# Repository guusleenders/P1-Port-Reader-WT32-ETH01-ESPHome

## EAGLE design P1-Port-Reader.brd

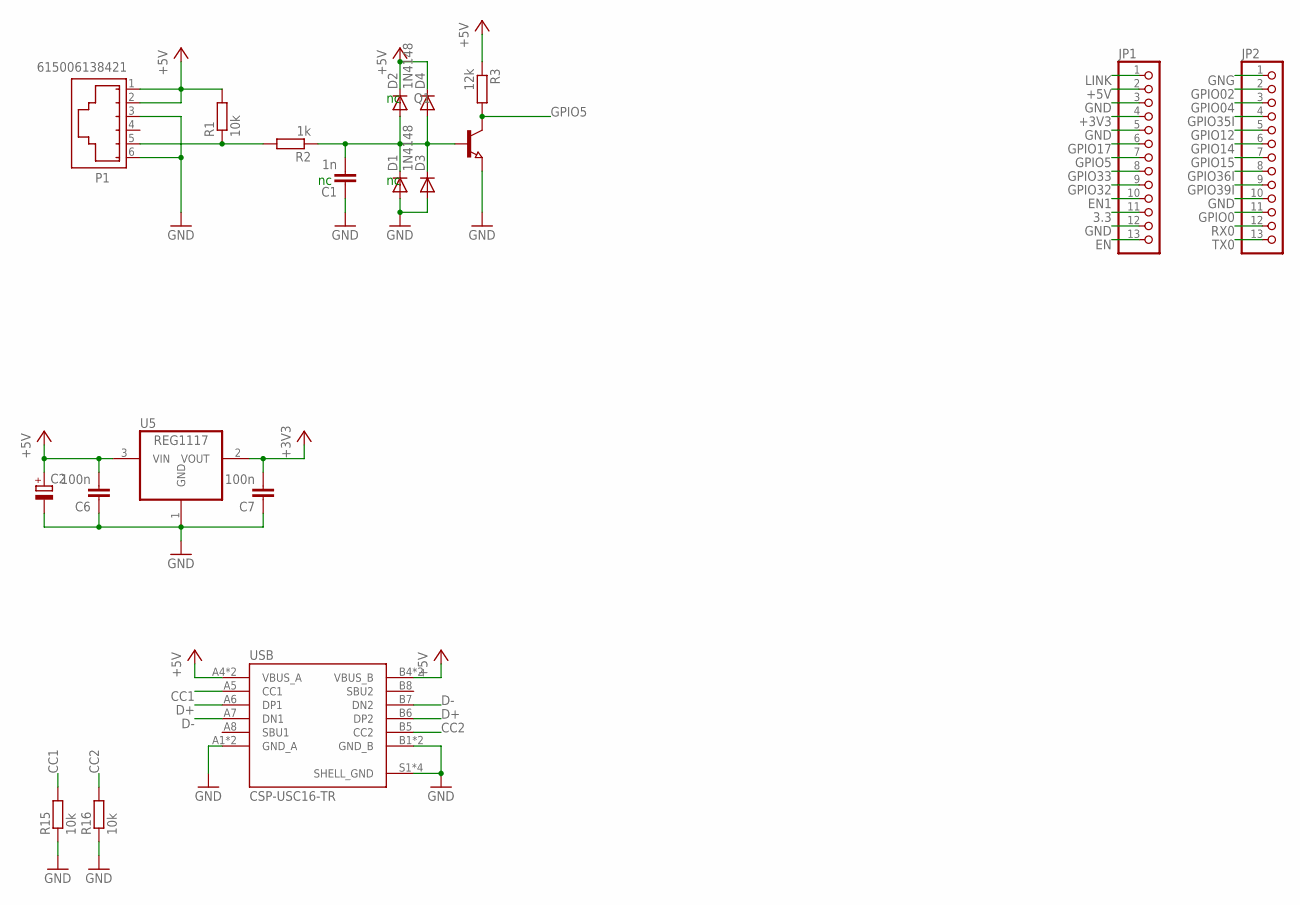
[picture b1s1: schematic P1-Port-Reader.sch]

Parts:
C1: 1n; C0805
C2: CPOL-EUE5-8.5; E5-8,5
C6, C7: 100n; C0805
D1, D2: 1N4148; SOD123
D3, D4: DIODE-SOD323-W; SOD323-W
JP1, JP2: PINHD-1X13; 1X13
P1: 615006138421
Q1: NPN-TRANSISTOR_SOT23; SOT23
R1: 10k; R0805
R2: 1k; R0805
R3: 12k; R0805
R15, R16: 10k; R0603
U5: REG1117; SOT223
USB: CSP-USC16-TR; VALCON_CSP-USC16-TR

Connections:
3.3: JP1.11
+3V3: C7.2, JP1.4, U5.2 (VOUT)
+5V: C2.+, C6.2, D2.C, D4.C, JP1.2, P1.1, P1.2, R1.2, R3.1, U5.3 (VIN), USB.A4 (VBUS_A), USB.A9 (VBUS_A), USB.B4 (VBUS_B), USB.B9 (VBUS_B)
CC1: R15.2, USB.A5 (CC1)
CC2: R16.2, USB.B5 (CC2)
D+: USB.A6 (DP1), USB.B6 (DP2)
D-: USB.A7 (DN1), USB.B7 (DN2)
EN: JP1.13
EN1: JP1.10
GND: C1.1, C2.-, C6.1, C7.1, D1.A, D3.A, JP1.3, JP1.5, JP1.12, JP2.10, P1.3, P1.6, Q1.2 (E), R15.1, R16.1, U5.1 (GND), USB.A1 (GND_A), USB.A12 (GND_A), USB.B1 (GND_B), USB.B12 (GND_B), USB.S1 (SHELL_GND), USB.S2 (SHELL_GND), USB.S3 (SHELL_GND), USB.S4 (SHELL_GND)
GNG: JP2.1
GPIO0: JP2.11
GPIO02: JP2.2
GPIO04: JP2.3
GPIO5: JP1.7, Q1.3 (C), R3.2
GPIO12: JP2.5
GPIO14: JP2.6
GPIO15: JP2.7
GPIO17: JP1.6
GPIO32: JP1.9
GPIO33: JP1.8
GPIO35I: JP2.4
GPIO36I: JP2.8
GPIO39I: JP2.9
LINK: JP1.1
unnamed: P1.5, R1.1, R2.2
unnamed: C1.2, D1.C, D2.A, D3.C, D4.A, Q1.1 (B), R2.1
RX0: JP2.12
TX0: JP2.13

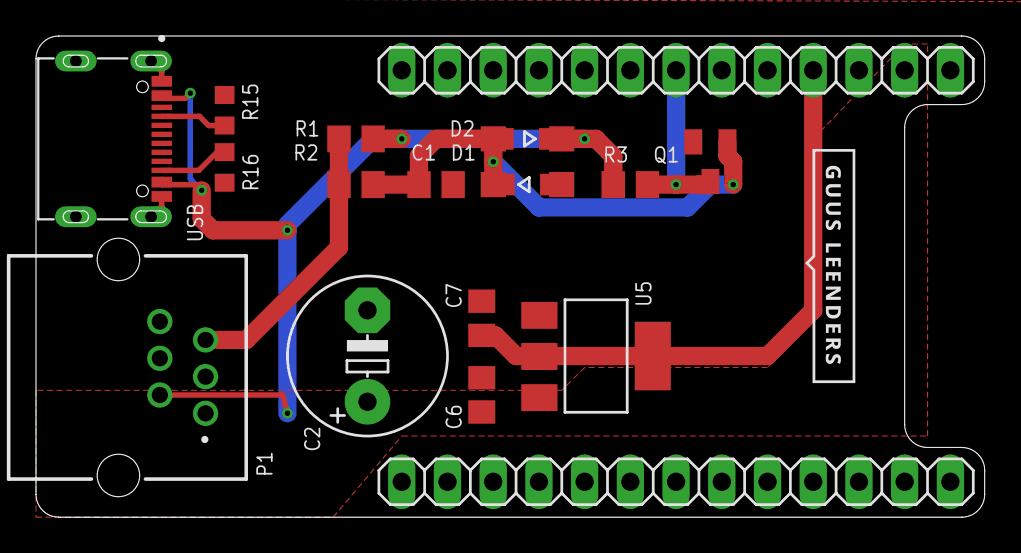
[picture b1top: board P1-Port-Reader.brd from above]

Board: 2 copper layers, 52.7 x 26.7 mm, 19 parts (0 on the bottom side), 10 nets.

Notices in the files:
parts and their libraries:
Eagle_WR-MJ: Copyright: Würth Elektronik
